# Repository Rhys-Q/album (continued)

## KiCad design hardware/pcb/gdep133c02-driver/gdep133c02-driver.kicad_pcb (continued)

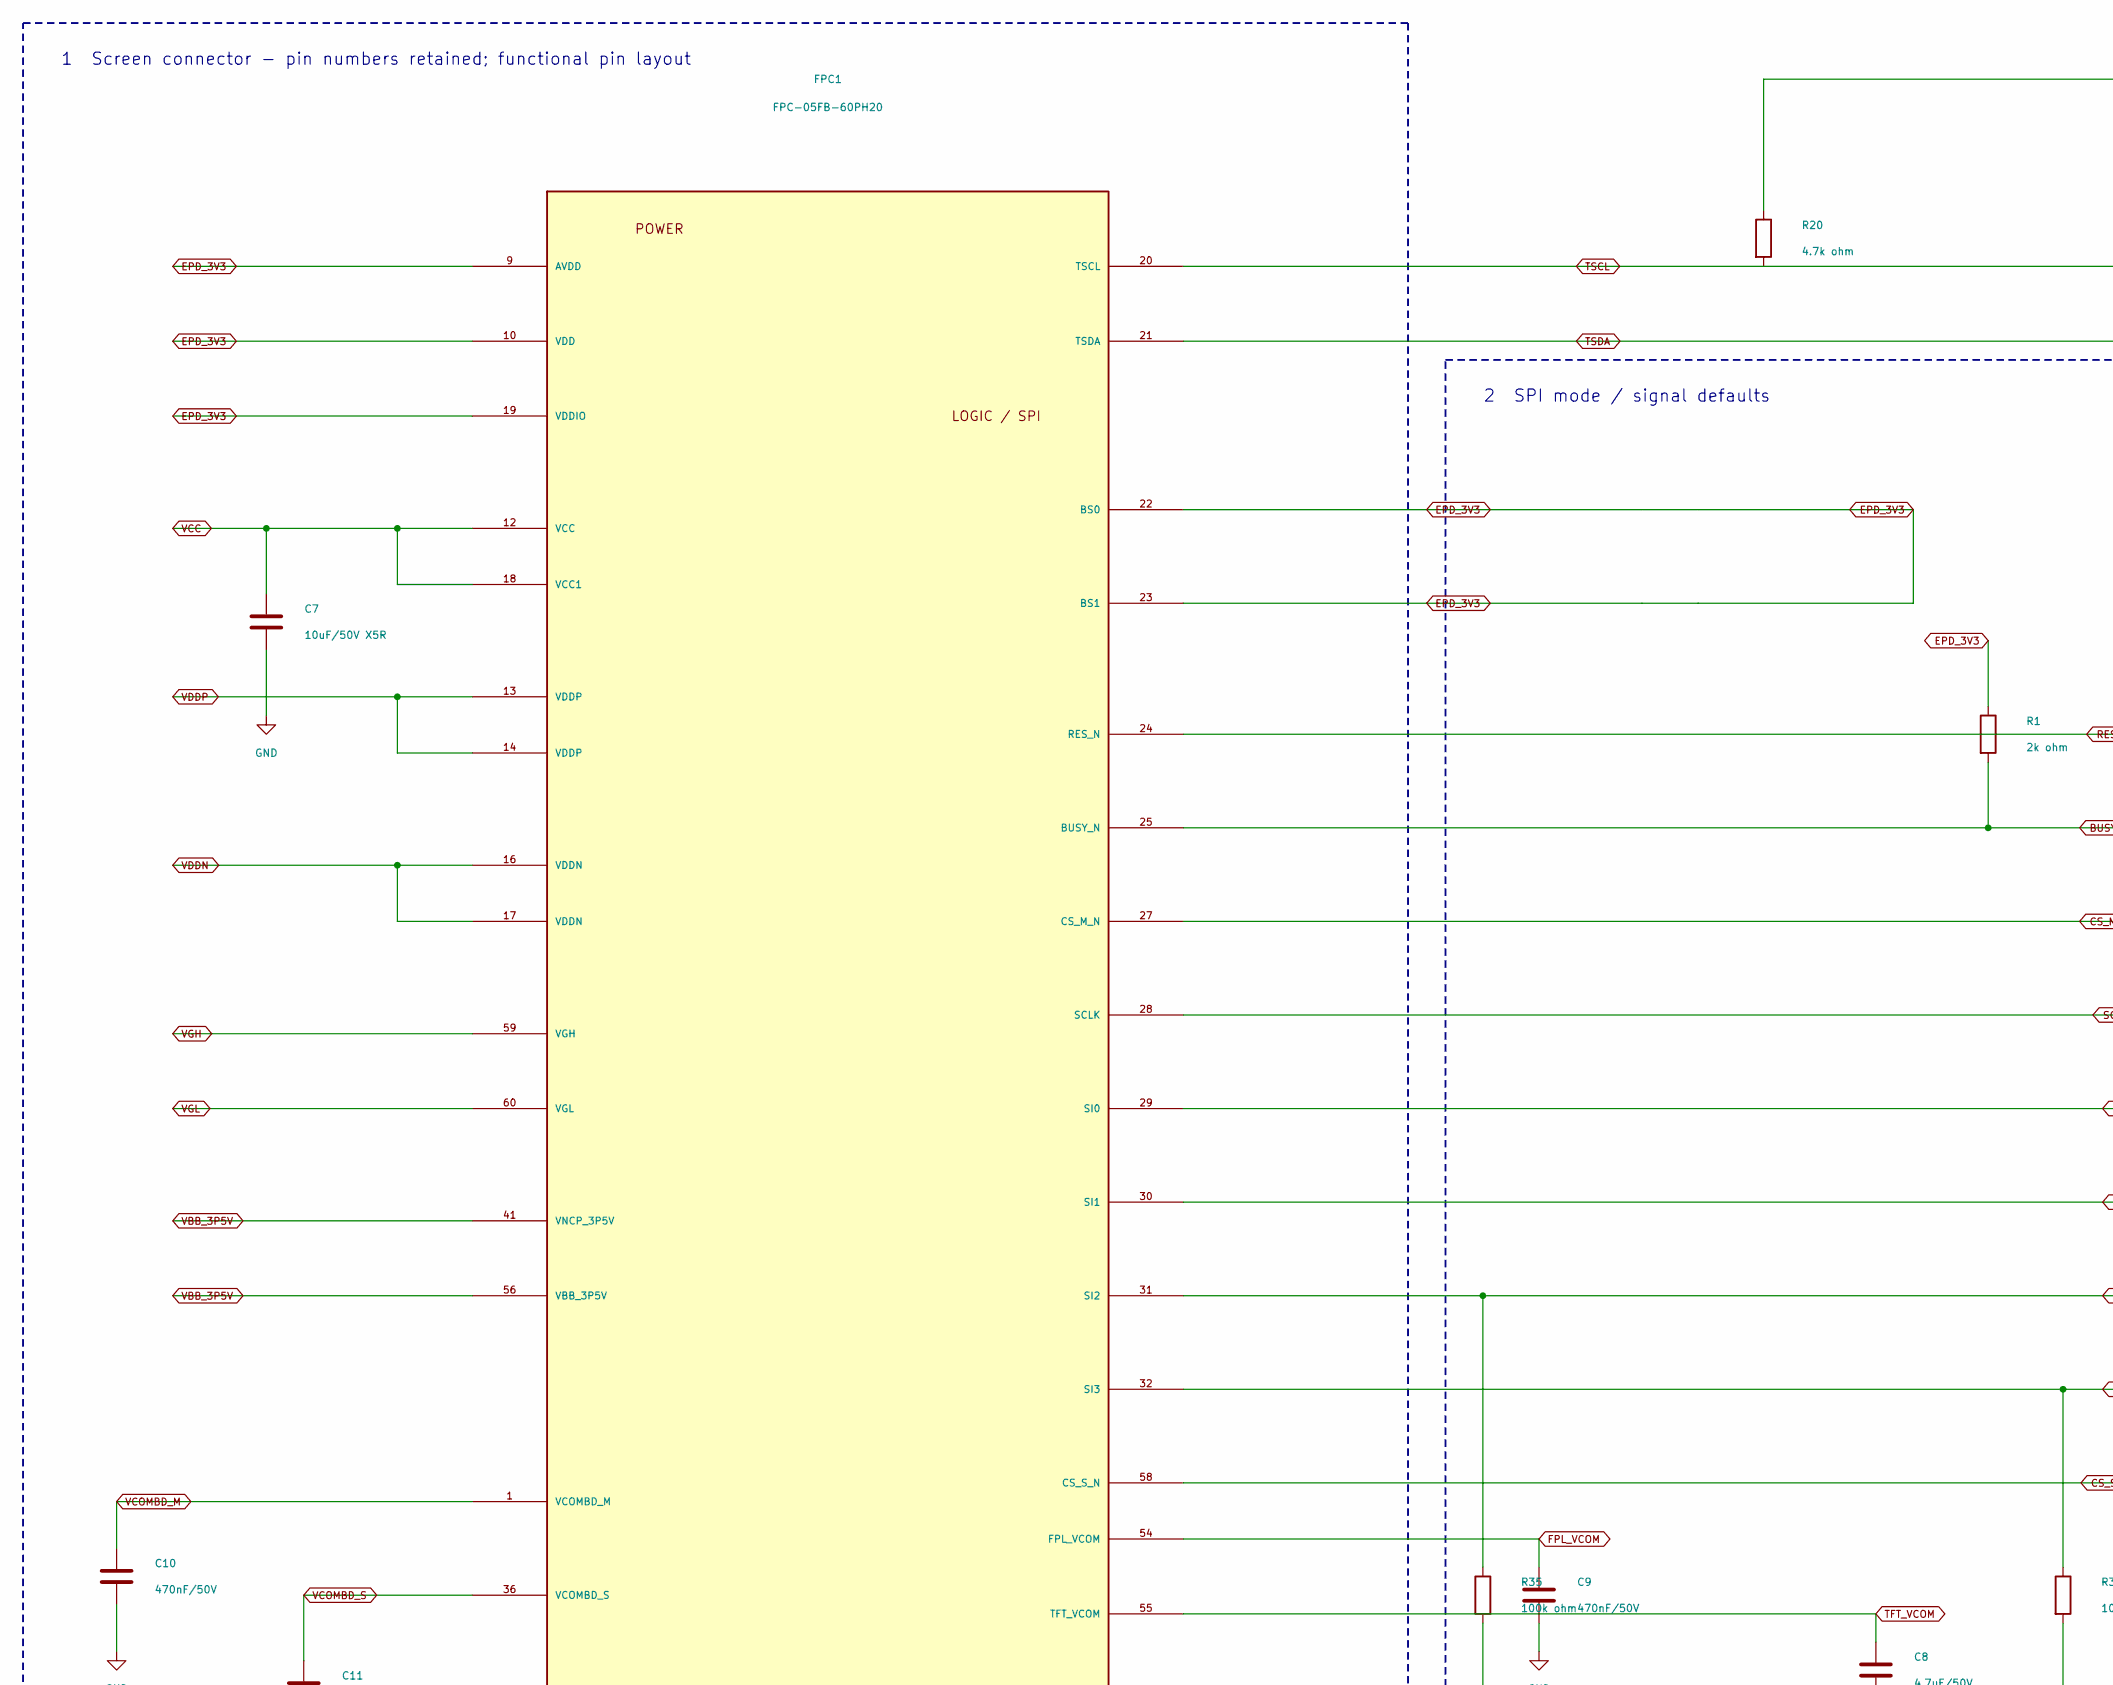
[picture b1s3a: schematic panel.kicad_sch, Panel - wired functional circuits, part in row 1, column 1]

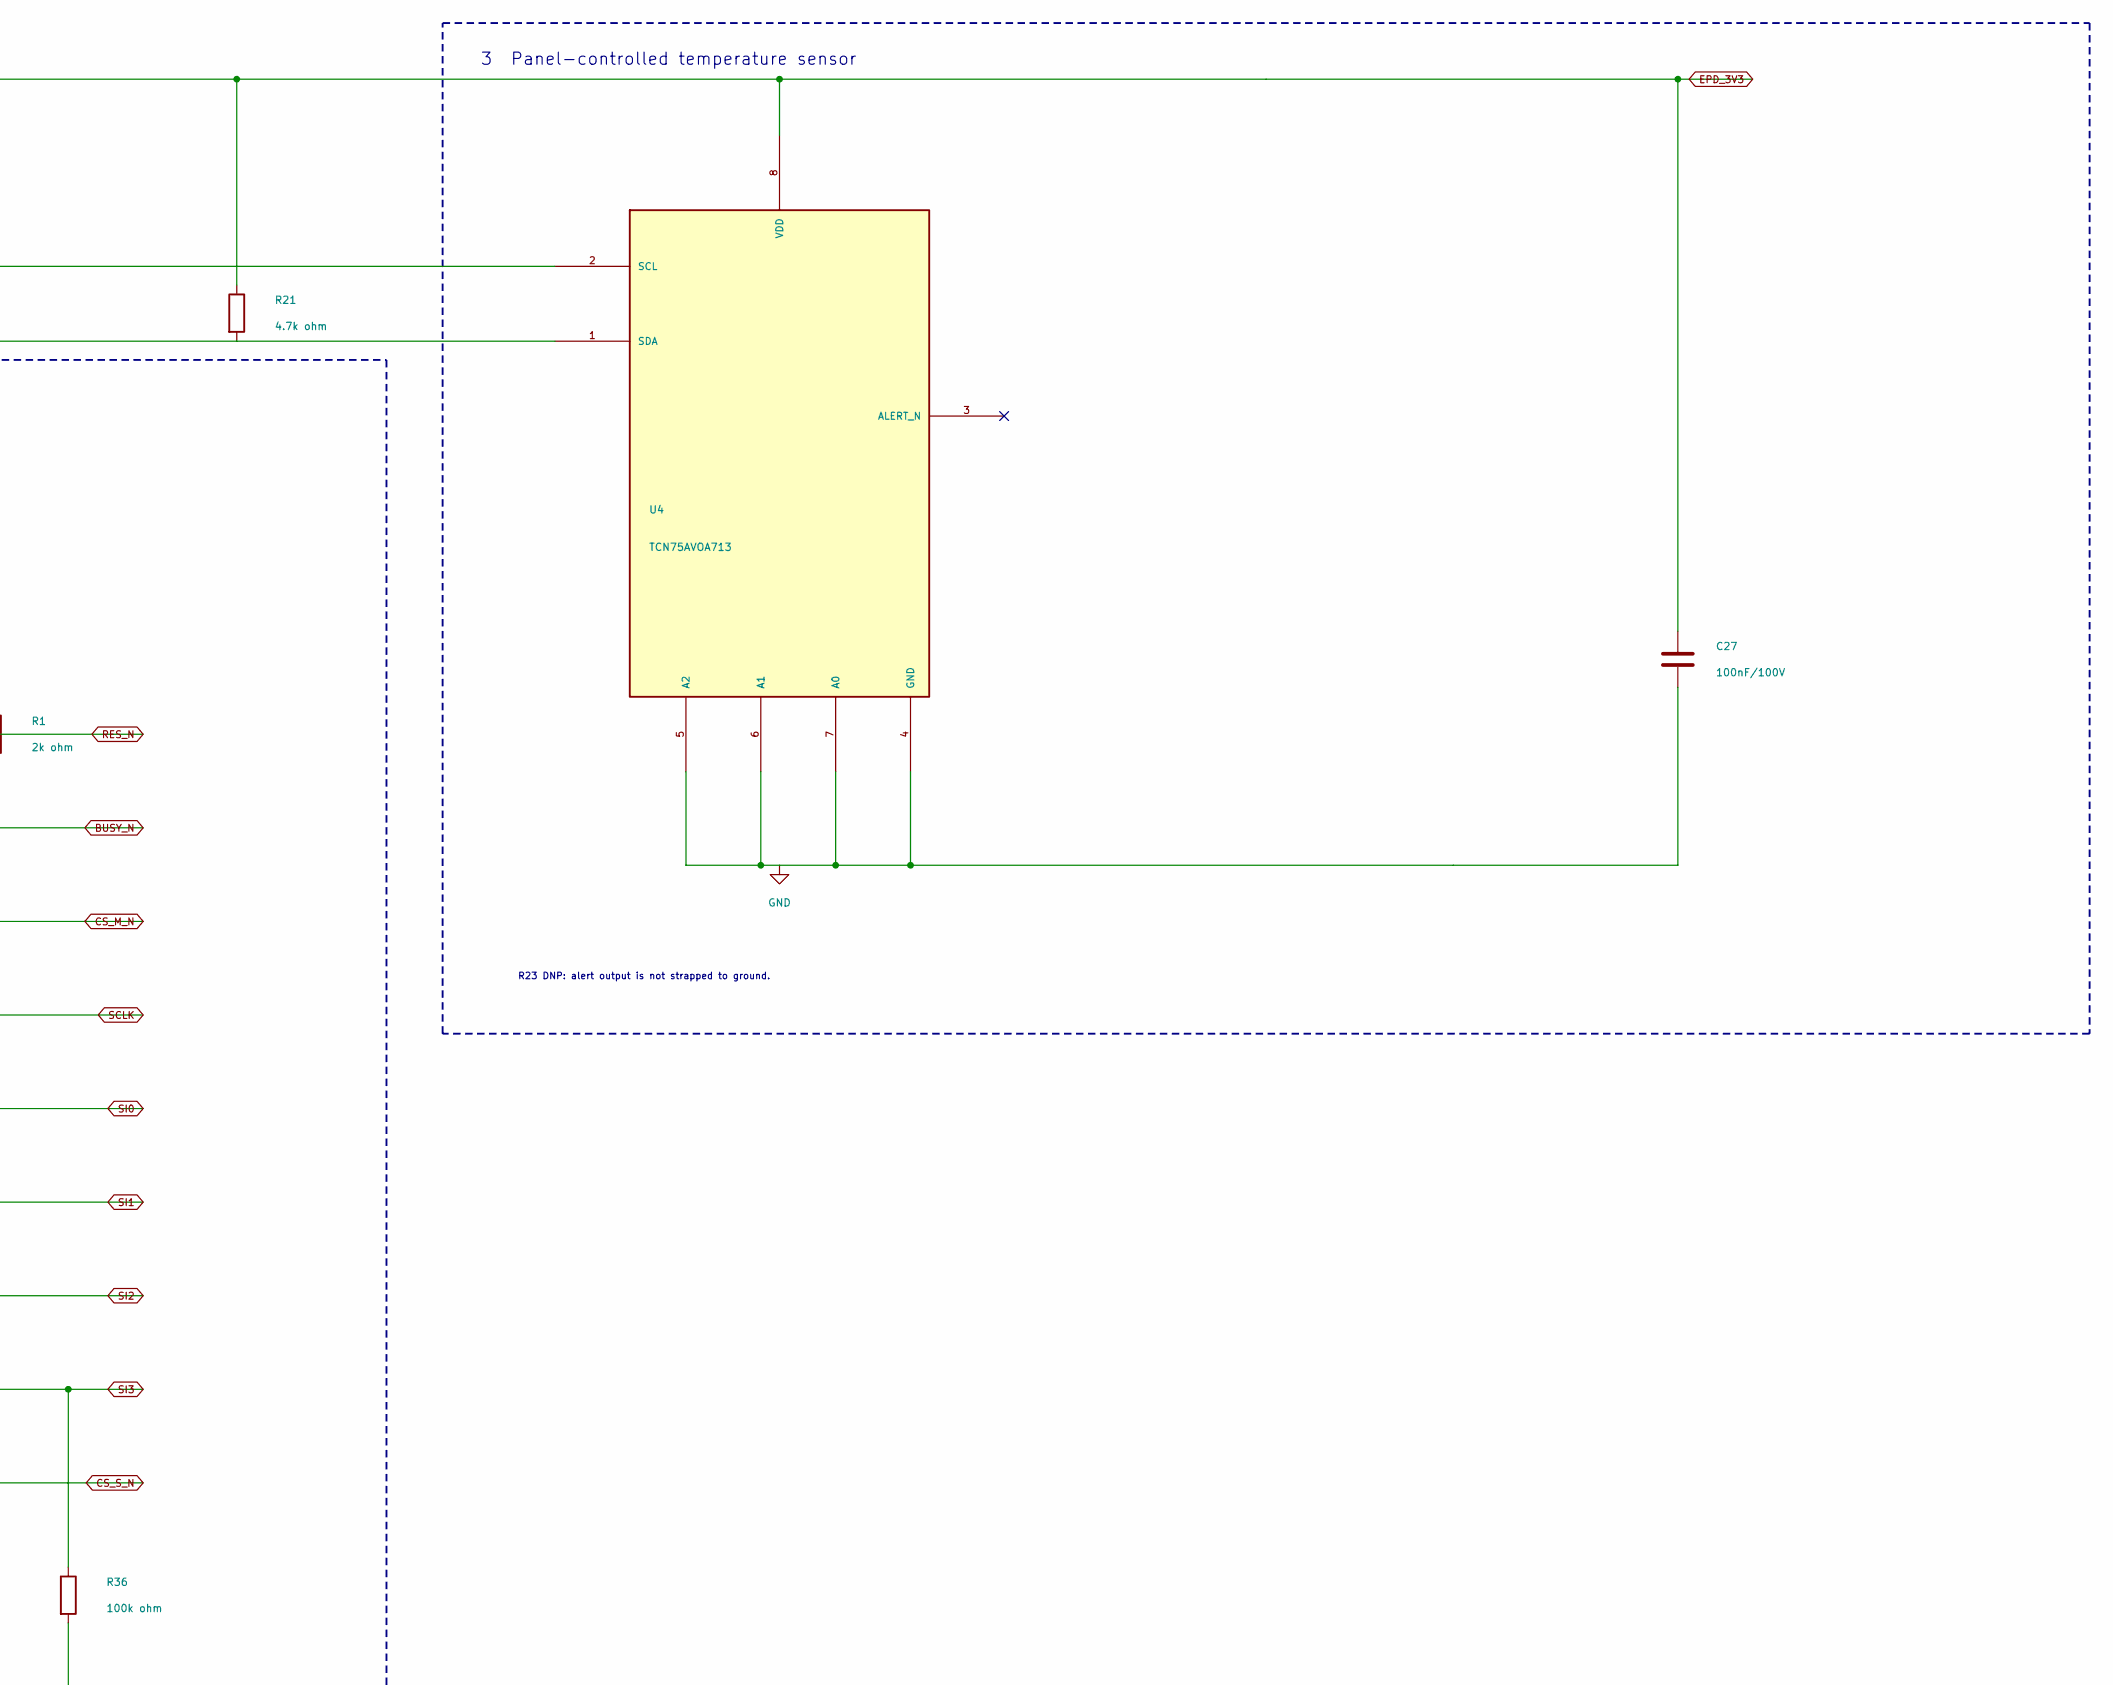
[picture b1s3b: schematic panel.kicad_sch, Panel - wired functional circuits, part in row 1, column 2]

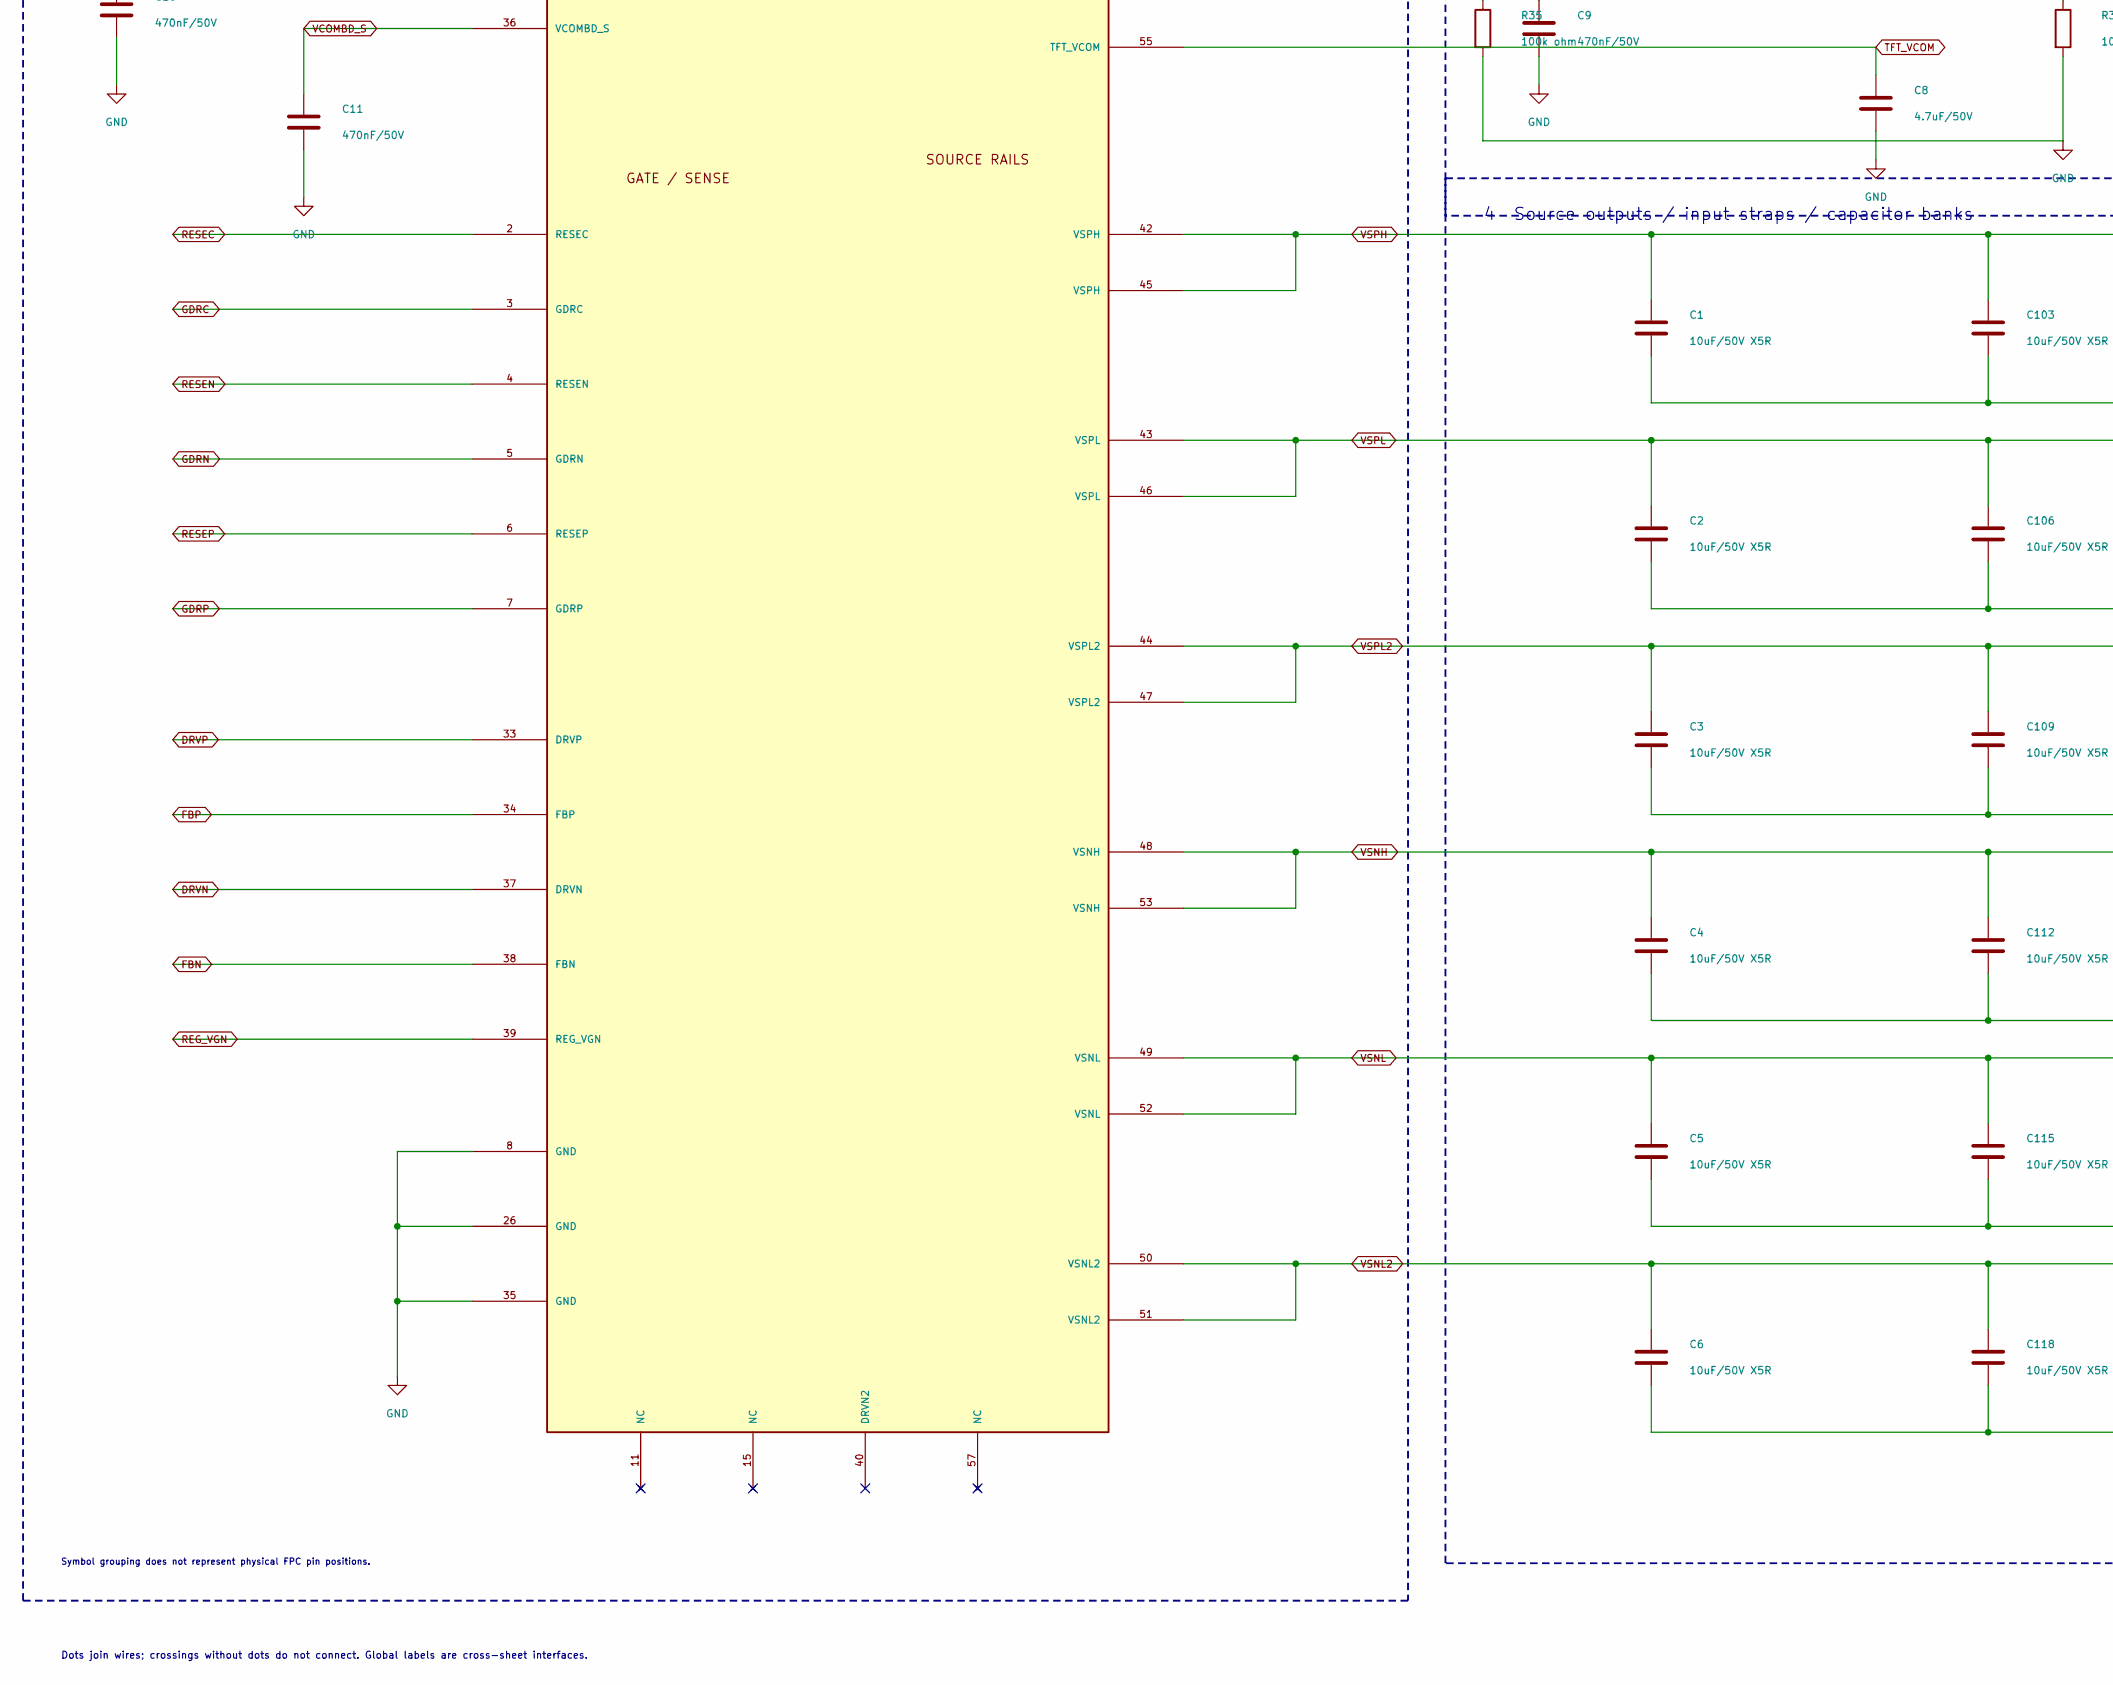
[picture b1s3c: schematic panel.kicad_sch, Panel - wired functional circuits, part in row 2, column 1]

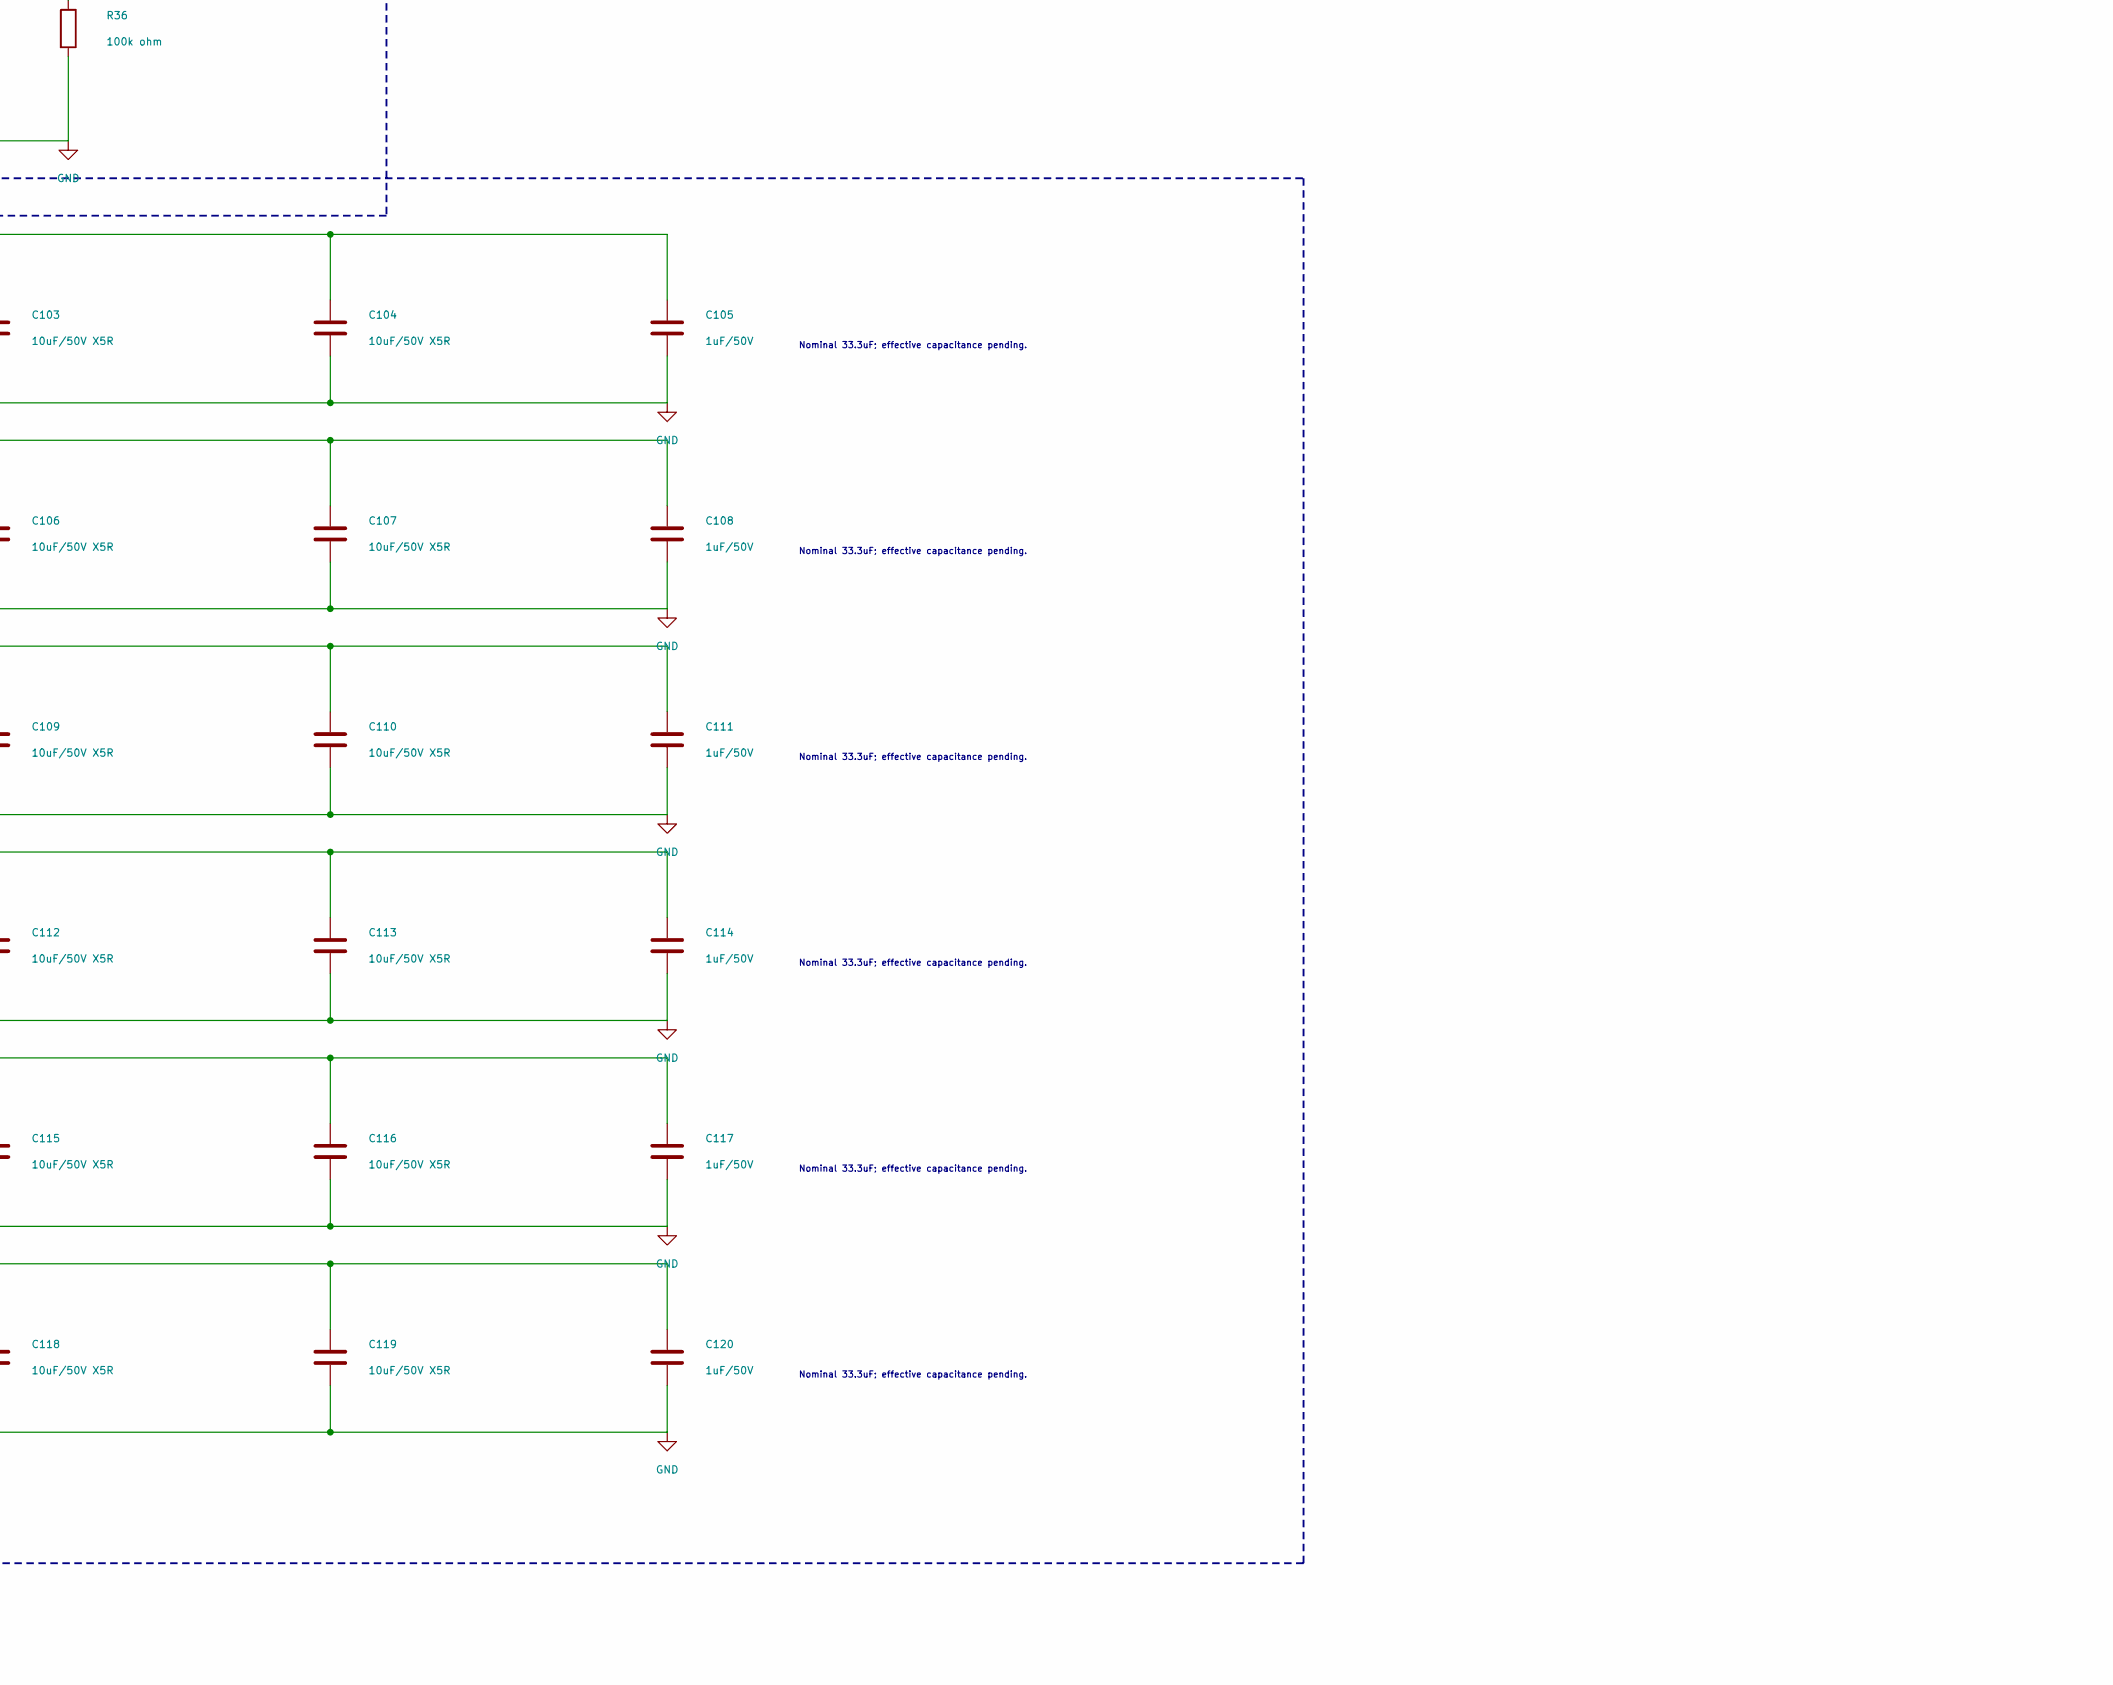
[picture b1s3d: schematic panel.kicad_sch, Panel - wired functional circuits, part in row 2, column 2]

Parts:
C1, C2, C3, C4, C5, C6, C7, C103, C104, C106, C107, C109, C110, C112, C113, C115, C116, C118, C119: 10uF/50V X5R; C_0805_HandSolder; MPN GRM21BR61H106KE43L; LCSC C440198
C8: 4.7uF/50V; C_1206_HandSolder; MPN 1206B475K500NT; LCSC C29823
C9, C10, C11: 470nF/50V; C_0805_HandSolder; MPN CL21B474KBFNNNE; LCSC C13967
C27: 100nF/100V; C_0805_HandSolder; MPN CL21B104KCFNNNE; LCSC C28233
C105, C108, C111, C114, C117, C120: 1uF/50V; C_0805_HandSolder; MPN CL21B105KBFNNNE; LCSC C28323
FPC1: FPC-05FB-60PH20; FPC_05FB_60PH20; MPN FPC-05FB-60PH20; LCSC C2856839
R1: 2k ohm; R_0805_HandSolder; MPN 0805W8F2001T5E; LCSC C17604
R20, R21: 4.7k ohm; R_0805_HandSolder; MPN 0805W8F4701T5E; LCSC C17673
R35, R36: 100k ohm; R_0805_HandSolder; MPN 0805W8F1003T5E; LCSC C149504
U4: TCN75AVOA713; Package_SO__SOIC-8_3.9x4.9mm_P1.27mm; MPN TCN75AVOA713; LCSC C144313

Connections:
BUSY_N: FPC1.25 (BUSY_N), R1.1; also elsewhere on the board
CS_M_N: FPC1.27 (CS_M_N); also elsewhere on the board
CS_S_N: FPC1.58 (CS_S_N); also elsewhere on the board
DRVN: FPC1.37 (DRVN); also elsewhere on the board
DRVP: FPC1.33 (DRVP); also elsewhere on the board
EPD_3V3: C27.1, FPC1.9 (AVDD), FPC1.10 (VDD), FPC1.19 (VDDIO), FPC1.22 (BS0), FPC1.23 (BS1), R1.2, R20.2, R21.2, U4.8 (VDD); also elsewhere on the board
FBN: FPC1.38 (FBN); also elsewhere on the board
FBP: FPC1.34 (FBP); also elsewhere on the board
FPL_VCOM: C9.1, FPC1.54 (FPL_VCOM)
GDRC: FPC1.3 (GDRC); also elsewhere on the board
GDRN: FPC1.5 (GDRN); also elsewhere on the board
GDRP: FPC1.7 (GDRP); also elsewhere on the board
GND: C1.2, C2.2, C3.2, C4.2, C5.2, C6.2, C7.2, C8.2, C9.2, C10.2, C11.2, C27.2, C103.2, C104.2, C105.2, C106.2, C107.2, C108.2, C109.2, C110.2, C111.2, C112.2, C113.2, C114.2, C115.2, C116.2, C117.2, C118.2, C119.2, C120.2, FPC1.8 (GND), FPC1.26 (GND), FPC1.35 (GND), R35.2, R36.2, U4.4 (GND), U4.5 (A2), U4.6 (A1), U4.7 (A0); also elsewhere on the board
REG_VGN: FPC1.39 (REG_VGN); also elsewhere on the board
RESEC: FPC1.2 (RESEC); also elsewhere on the board
RESEN: FPC1.4 (RESEN); also elsewhere on the board
RESEP: FPC1.6 (RESEP); also elsewhere on the board
RES_N: FPC1.24 (RES_N); also elsewhere on the board
SCLK: FPC1.28 (SCLK); also elsewhere on the board
SI0: FPC1.29 (SI0); also elsewhere on the board
SI1: FPC1.30 (SI1); also elsewhere on the board
SI2: FPC1.31 (SI2), R35.1
SI3: FPC1.32 (SI3), R36.1
TFT_VCOM: C8.1, FPC1.55 (TFT_VCOM); also elsewhere on the board
TSCL: FPC1.20 (TSCL), R20.1, U4.2 (SCL)
TSDA: FPC1.21 (TSDA), R21.1, U4.1 (SDA)
VBB_3P5V: FPC1.41 (VNCP_3P5V), FPC1.56 (VBB_3P5V); also elsewhere on the board
VCC: C7.1, FPC1.12 (VCC), FPC1.18 (VCC1); also elsewhere on the board
VCOMBD_M: C10.1, FPC1.1 (VCOMBD_M)
VCOMBD_S: C11.1, FPC1.36 (VCOMBD_S)
VDDN: FPC1.16 (VDDN), FPC1.17 (VDDN); also elsewhere on the board
VDDP: FPC1.13 (VDDP), FPC1.14 (VDDP); also elsewhere on the board
VGH: FPC1.59 (VGH); also elsewhere on the board
VGL: FPC1.60 (VGL); also elsewhere on the board
VSNH: C4.1, C112.1, C113.1, C114.1, FPC1.48 (VSNH), FPC1.53 (VSNH); also elsewhere on the board
VSNL: C5.1, C115.1, C116.1, C117.1, FPC1.49 (VSNL), FPC1.52 (VSNL); also elsewhere on the board
VSNL2: C6.1, C118.1, C119.1, C120.1, FPC1.50 (VSNL2), FPC1.51 (VSNL2); also elsewhere on the board
VSPH: C1.1, C103.1, C104.1, C105.1, FPC1.42 (VSPH), FPC1.45 (VSPH); also elsewhere on the board
VSPL: C2.1, C106.1, C107.1, C108.1, FPC1.43 (VSPL), FPC1.46 (VSPL); also elsewhere on the board
VSPL2: C3.1, C109.1, C110.1, C111.1, FPC1.44 (VSPL2), FPC1.47 (VSPL2); also elsewhere on the board

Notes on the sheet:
1 Screen connector - pin numbers retained; functional pin layout
Symbol grouping does not represent physical FPC pin positions.
2 SPI mode / signal defaults
3 Panel-controlled temperature sensor
R23 DNP: alert output is not strapped to ground.
4 Source outputs / input straps / capacitor banks
Nominal 33.3uF; effective capacitance pending.
Dots join wires; crossings without dots do not connect. Global labels are cross-sheet interfaces.
